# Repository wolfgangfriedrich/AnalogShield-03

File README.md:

# AnalogShield-03
Arduino Schield Pixi Analog I/O 20channel Eagle design files

Project is hosted at HackADay.io
https://hackaday.io/project/4397-pixi-analog-shield

Arduino library and sample code are storedin a separate repository
https://github.com/wolfgangfriedrich/Pixi_demo

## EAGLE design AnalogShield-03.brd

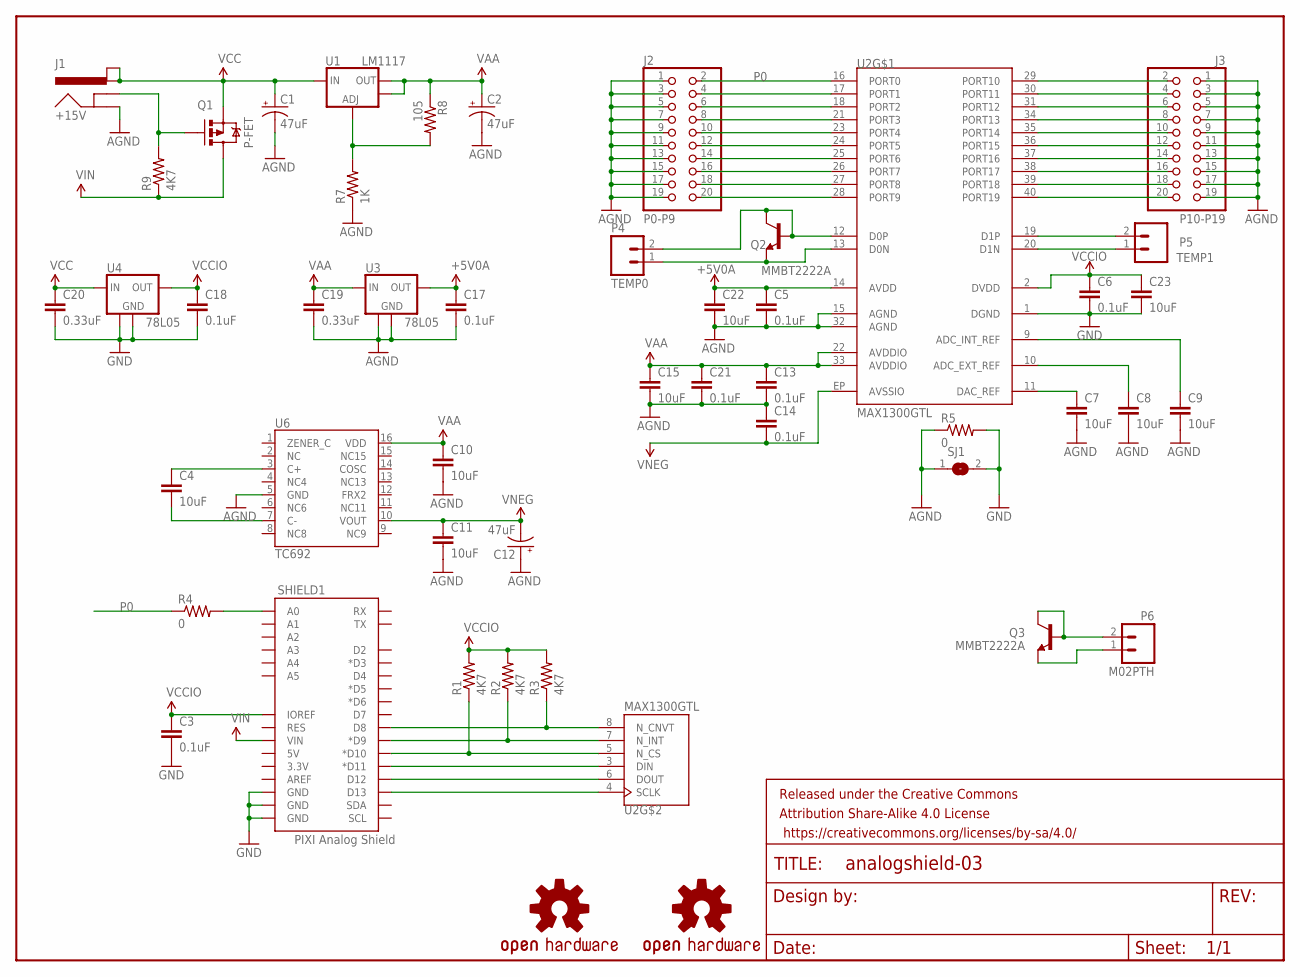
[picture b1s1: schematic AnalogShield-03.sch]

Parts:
C1, C2, C12: 47uF; PANASONIC_D; MFR1PN EEE-FPC470UAR
C3, C5, C6, C13, C14, C17, C18, C21: 0.1uF; 0603-CAP
C4, C7, C8, C9, C10, C11, C15, C22, C23: 10uF; 1206
C19, C20: 0.33uF; 0603-CAP
FRAME1: FRAME-LETTER; CREATIVE_COMMONS
J1: +15V; POWER_JACK_SMD; MFR1PN ADC-028-01
J2: P0-P9; 2X10_SMD; MFR1PN 15912200
J3: P10-P19; 2X10_SMD; MFR1PN 15912200
LOGO1, LOGO2: OSHW-LOGOS; OSHW-LOGO-S
P4: TEMP0; 1X02
P5: TEMP1; JST-2-SMD-VERT; MFR1PN B2B-PH-SM4-TB
P6: M02PTH; 1X02
Q1: P-FET; SOT23-3; MFR1PN IRLML2244
Q2, Q3: MMBT2222A; SOT23-3; MFR1PN MMBT3904
R1, R2, R3, R9: 4K7; 0603
R4, R5: 0; 0603
R7: 1K; 0603-RES
R8: 105; 0603-RES
SHIELD1: PIXI Analog Shield; UNO_R3_SHIELD_NOLABELS
SJ1: SJ
U1: LM1117; SOT223; MFR1PN LD1117STR
U2: MAX1300GTL; QFN50P600X600X75-41; MFR1PN MAX11300GTL+
U3, U4: 78L05; SOT89; MFR1PN MC78L05ACH
U6: TC692; SO16L; MFR1PN TC962COE

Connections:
+5V0A: C5.1, C17.1, C22.1, U2.14 (AVDD), U3.1 (OUT)
ADJ: R7.2, R8.2, U1.1 (ADJ)
AGND: C1.-, C2.-, C5.2, C7.2, C8.2, C9.2, C10.2, C11.2, C12.+, C13.2, C14.1, C15.2, C17.2, C19.2, C21.2, C22.2, J1.GND, J2.1, J2.3, J2.5, J2.7, J2.9, J2.11, J2.13, J2.15, J2.17, J2.19, J3.1, J3.3, J3.5, J3.7, J3.9, J3.11, J3.13, J3.15, J3.17, J3.19, R5.1, R7.1, SJ1.1, U2.15 (AGND), U2.32 (AGND), U3.2 (GND), U3.4 (GND), U6.5 (GND)
C+: C4.1, U6.3 (C+)
C-: C4.2, U6.7 (C-)
DIN: SHIELD1.D11 (*D11), U2.3 (DIN)
DOUT: SHIELD1.D12, U2.6 (DOUT)
GND: C3.2, C6.2, C18.2, C20.2, C23.2, R5.2, SHIELD1.GND@0 (GND), SHIELD1.GND@1 (GND), SHIELD1.GND@2 (GND), SJ1.2, U2.1 (DGND), U4.2 (GND), U4.4 (GND)
unnamed: R2.1, SHIELD1.D9 (*D9), U2.7 (N_INT)
unnamed: R1.1, SHIELD1.D10 (*D10), U2.5 (N_CS)
unnamed: SHIELD1.D13, U2.4 (SCLK)
unnamed: J2.4, U2.17 (PORT1)
unnamed: J2.6, U2.18 (PORT2)
unnamed: J2.8, U2.21 (PORT3)
unnamed: J2.10, U2.23 (PORT4)
unnamed: J2.12, U2.24 (PORT5)
unnamed: J2.14, U2.25 (PORT6)
unnamed: J2.16, U2.26 (PORT7)
unnamed: J2.18, U2.27 (PORT8)
unnamed: J2.20, U2.28 (PORT9)
unnamed: J3.2, U2.29 (PORT10)
unnamed: J3.4, U2.30 (PORT11)
unnamed: J3.6, U2.31 (PORT12)
unnamed: J3.8, U2.34 (PORT13)
unnamed: J3.10, U2.35 (PORT14)
unnamed: J3.12, U2.36 (PORT15)
unnamed: J3.14, U2.37 (PORT16)
unnamed: J3.16, U2.38 (PORT17)
unnamed: J3.18, U2.39 (PORT18)
unnamed: J3.20, U2.40 (PORT19)
unnamed: P6.2, Q3.1 (B), Q3.3 (C)
unnamed: P6.1, Q3.2 (E)
unnamed: P4.1, Q2.2 (E), U2.13 (D0N)
unnamed: P4.2, Q2.1 (B), Q2.3 (C), U2.12 (D0P)
unnamed: P5.1 (2), U2.20 (D1N)
unnamed: P5.2 (1), U2.19 (D1P)
unnamed: C7.1, U2.11 (DAC_REF)
unnamed: J1.P$4 (GNDBREAK), Q1.1 (G), R9.2
unnamed: C8.1, U2.10 (ADC_EXT_REF)
unnamed: R4.2, SHIELD1.A0
unnamed: C9.1, U2.9 (ADC_INT_REF)
N_CNVT: R3.1, SHIELD1.D8, U2.8 (N_CNVT)
P0: J2.2, R4.1, U2.16 (PORT0)
VAA: C2.+, C10.1, C13.1, C15.1, C19.1, C21.1, R8.1, U1.2 (OUT), U1.4 (OUT), U2.22 (AVDDIO), U2.33 (AVDDIO), U3.3 (IN), U6.16 (VDD)
VCC: C1.+, C20.1, J1.VIN0$1 (PWR), J1.VIN0$2 (PWR1), Q1.2 (S), U1.3 (IN), U4.3 (IN)
VCCIO: C3.1, C6.1, C18.1, C23.1, R1.2, R2.2, R3.2, SHIELD1.IOREF, U2.2 (DVDD), U4.1 (OUT)
VIN: Q1.3 (D), R9.1, SHIELD1.VIN
VNEG: C11.1, C12.-, C14.2, U2.EP (AVSSIO), U6.10 (VOUT)

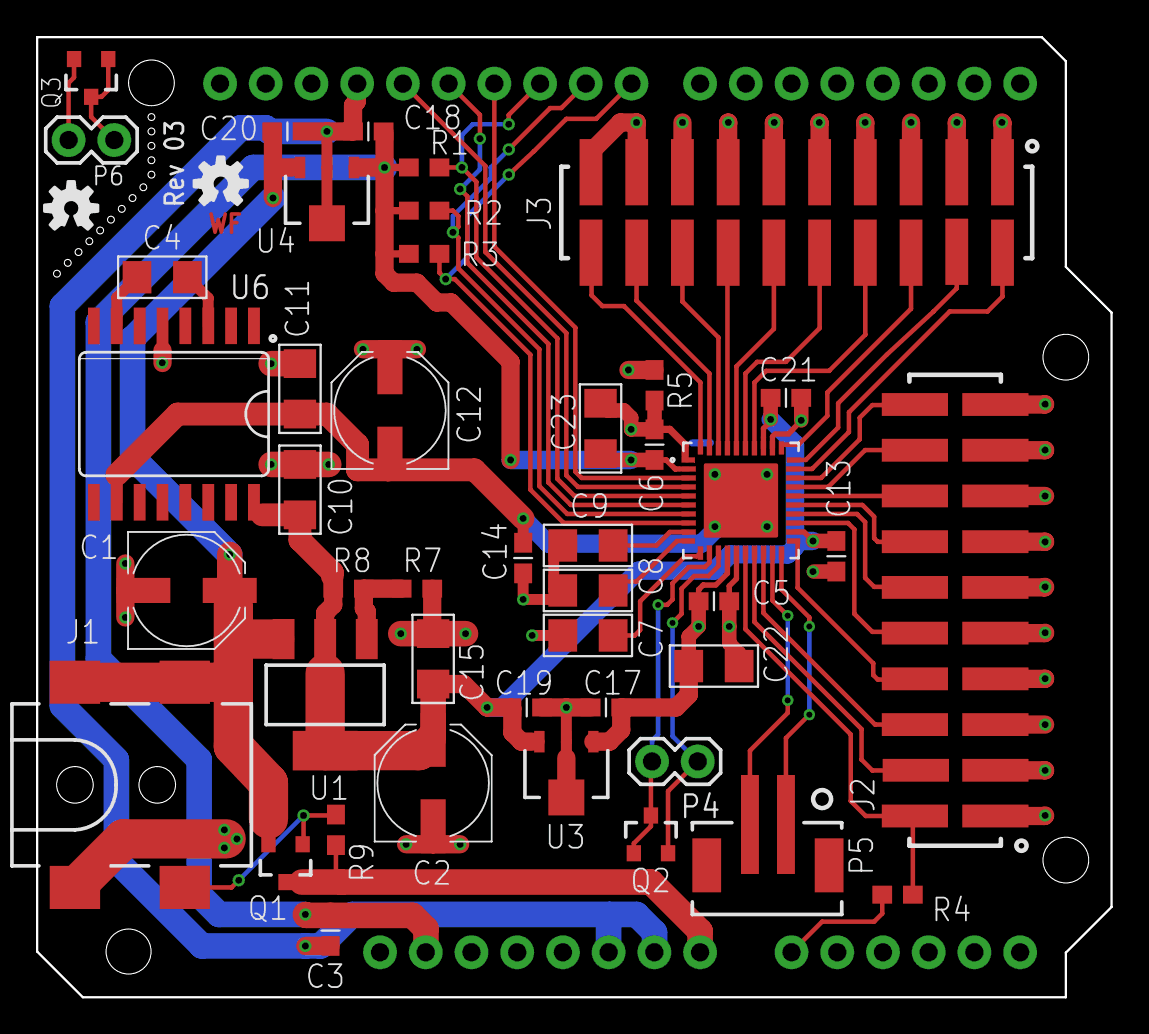
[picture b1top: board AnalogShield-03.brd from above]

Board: 2 copper layers, 59.7 x 53.3 mm, 49 parts (1 on the bottom side), 48 nets.

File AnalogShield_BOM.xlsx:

Qty | Value | Device | Package | Parts | Description | MFR1 | MFR1PN | MFR2 | MFR2PN | MFR3 | MFR3PN | PROD_ID | VALUE
3 | 47uF | 47UF-50V-20%(ELECT) | PANASONIC_D | C1, C2, C12 | CAP-10547 | Panasonic | EEE-FPC470UAR |  |  |  |  | CAP-10547
2 | 0.33uF | 0.33UF-25V(+20/-20%)(0603) | 0603-CAP | C19, C20 | Ceramic |  |  |  |  |  |  |  | 0.33uF
8 | 0.1uF | 0.1UF-25V(+80/-20%)(0603) | 0603-CAP | C3, C5, C6, C13, C14, C17, C18, C21 | CAP-00810 |  |  |  |  |  |  | CAP-00810 | 0.1uF
9 | 10uF | 10UF-25V-10%(1206) | 1206 | C4, C7, C8, C9, C10, C11, C15, C22, C23 | 10uF | Taiyo Yuden | TMK316B7106KL-TD | Samsung | CL31B106KAHNNNE |  |  |  | 10uF
1 | FRAME-LETTER | FRAME-LETTER | CREATIVE_COMMONS | FRAME1 | Schematic Frame
1 | +15V | POWER_JACKSMD | POWER_JACK_SMD | J1 | Power Jack | Adam Tech | ADC-028-01 | Cui | PJ-002AH-SMT-TR | Sparkfun | PRT-12748 | CONN-08106 | 5.5x2.1mm Barrel
1 | P0-P9 | PINHD-2X10_SMD | 2X10_SMD | J2 | PIN HEADER | Molex | 15912200
1 | P10-P19 | PINHD-2X10_SMD | 2X10_SMD | J3 | PIN HEADER | Molex | 15912200
2 | OSHW-LOGOS | OSHW-LOGOS | OSHW-LOGO-S | LOGO1, LOGO2 | Open Source Hardware Logo This logo indicates the piece of hardware it is found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
1 | TEMP0 | M02PTH | 1X02 | P4 | Standard 2-pin 0.1 header. Use with"
1 | TEMP1 | M024UCON-15767 | JST-2-SMD-VERT | P5 | Standard 2-pin 0.1 header. Use with" | JST | B2B-PH-SM4-TB
1 | M02PTH | M02PTH | 1X02 | P6 | Standard 2-pin 0.1 header. Use with"
1 | P-FET | P-FET | SOT23-3 | Q1 | Generic PMOSFET | International Rectifier | IRLML2244 |  |  |  |  | TRANS-08285
2 | MMBT2222A | TRANSISTOR_NPNMMBT2222A | SOT23-3 | Q2, Q3 | Generic NPN BJT | NXP | MMBT3904 | ON Semi | MMBT2222A |  |  | TRANS-08049 | MMBT2222A
4 | 4K7 | 4.7KOHM1/10W1%(0603) | 603 | R1, R2, R3, R9 | RES-07857 |  |  |  |  |  |  | RES-07857
2 | 0 | 0OHM-1/10W-5%(0603) | 603 | R4, R5 | RES-08609 |  |  |  |  |  |  | RES-08609 | 0
1 | 1K | 1KOHM-1/10W-1%(0603) | 0603-RES | R7 | RES-07856 |  |  |  |  |  |  | RES-07856 | 1K
1 | 105 | 105OHM-1/10W-1%(0603) | 0603-RES | R8 | RES-10751 |  |  |  |  |  |  | RES-10751 | 105
1 | PIXI Analog Shield | ARDUINO_R3_SHIELDNOLABELS | UNO_R3_SHIELD_NOLABELS | SHIELD1 | Shield form compatible with the Arduino Uno R3.
1 |  | SJ | SJ | SJ1 | SMD solder JUMPER
1 | LM1117 | V_REG_LM1117SOT223 | SOT223 | U1 | Voltage Regulator LM1117 | ST Micro | LD1117STR |  |  |  |  | VREG-08170
1 | MAX1300GTL | MAX11300GTL | QFN50P600X600X75-41 | U2 | PIXI, 20-Port Programmable Mixed-Signal I/O with | Maxim | MAX11300GTL+
2 | 78L05 | 78L05 | SOT89 | U3, U4 |  | Fairchild | MC78L05ACH
1 | TC692 | TC962COE | SO16L | U6 | 80mA Charge Pump DC-to-DC Converter | Microchip | TC962COE

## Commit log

2015-12-27 :confetti_ball: Added .gitattributes & .gitignore files
2015-12-27 Schematics and Layout
    done with Eagle 7.2
2015-12-27 Gerber Data
2015-12-27 Assembly Data
    Schematics and assembly drawing as PDF, Bill of materials

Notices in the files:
parts and their libraries:
SparkFun-Capacitors: Licensing: Creative Commons ShareAlike 4.0 International - https://creativecommons.org/licenses/by-sa/4.0
SparkFun-Aesthetics: Released under the Creative Commons Attribution Share-Alike 4.0 License
SparkFun-Aesthetics: https://creativecommons.org/licenses/by-sa/4.0
